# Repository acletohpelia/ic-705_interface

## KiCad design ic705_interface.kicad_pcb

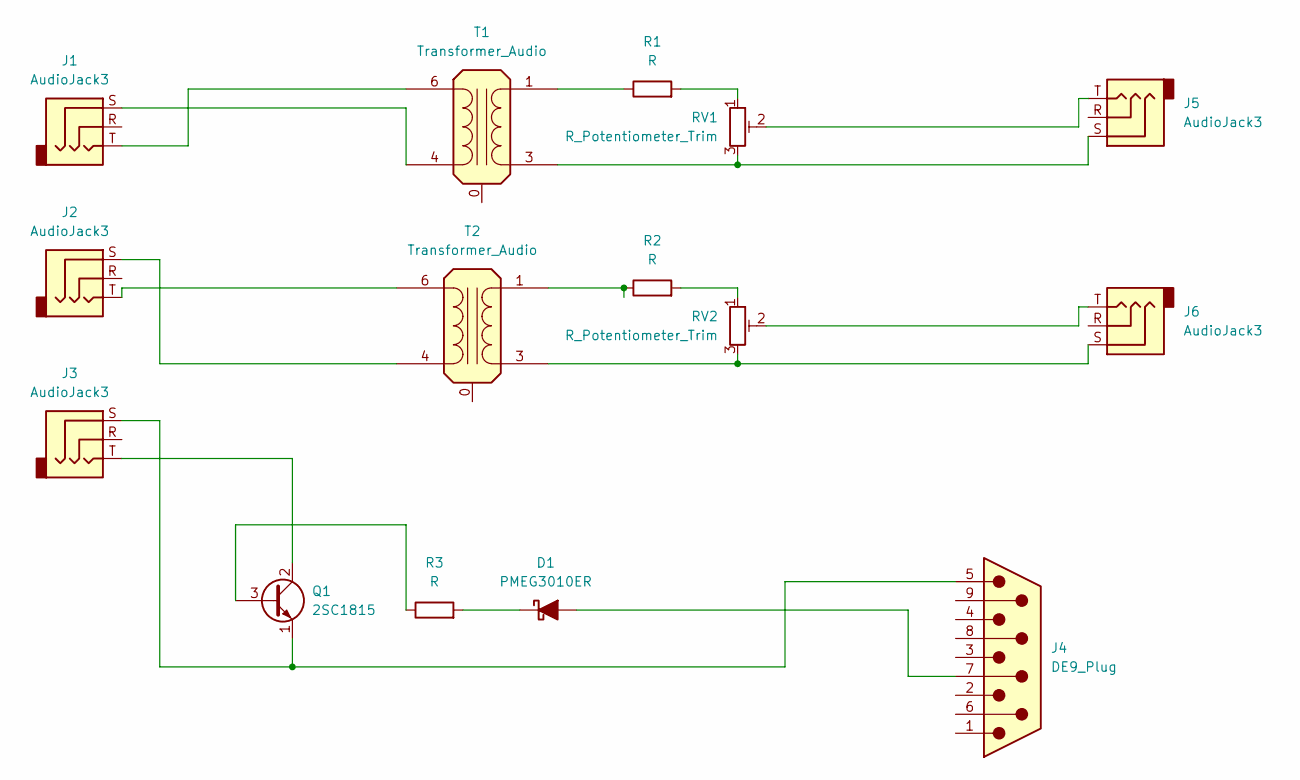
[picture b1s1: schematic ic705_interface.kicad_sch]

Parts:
D1: PMEG3010ER; D_DO-201AE_P15.24mm_Horizontal
J1, J2, J3, J5, J6: AudioJack3; Jack_3.5mm_CUI_SJ1-3533NG_Horizontal
J4: DE9_Plug; DSUB-9_Female_Vertical_P2.77x2.84mm_MountingHoles
Q1: 2SC1815; TO-92_Inline
R1, R2, R3: R; R_Axial_DIN0204_L3.6mm_D1.6mm_P1.90mm_Vertical
RV1, RV2: R_Potentiometer_Trim; Potentiometer_Piher_PT-10-V05_Vertical
T1, T2: Transformer_Audio; Transformer_NF_ETAL_1-1_P1200

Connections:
unnamed: D1.2 (A), J4.7
unnamed: D1.1 (K), R3.2
unnamed: J5.T, RV1.2
unnamed: J6.T, RV2.2
unnamed: Q1.3 (B), R3.1
unnamed: J3.T, Q1.2 (C)
unnamed: J3.S, J4.5, Q1.1 (E)
unnamed: R1.2, RV1.1
unnamed: R2.2, RV2.1
unnamed: J1.T, T1.6 (AA)
unnamed: J1.S, T1.4 (AB)
unnamed: J5.S, RV1.3, T1.3 (SA)
unnamed: R1.1, T1.1 (SB)
unnamed: J2.T, T2.6 (AA)
unnamed: J2.S, T2.4 (AB)
unnamed: J6.S, RV2.3, T2.3 (SA)
unnamed: R2.1, T2.1 (SB)

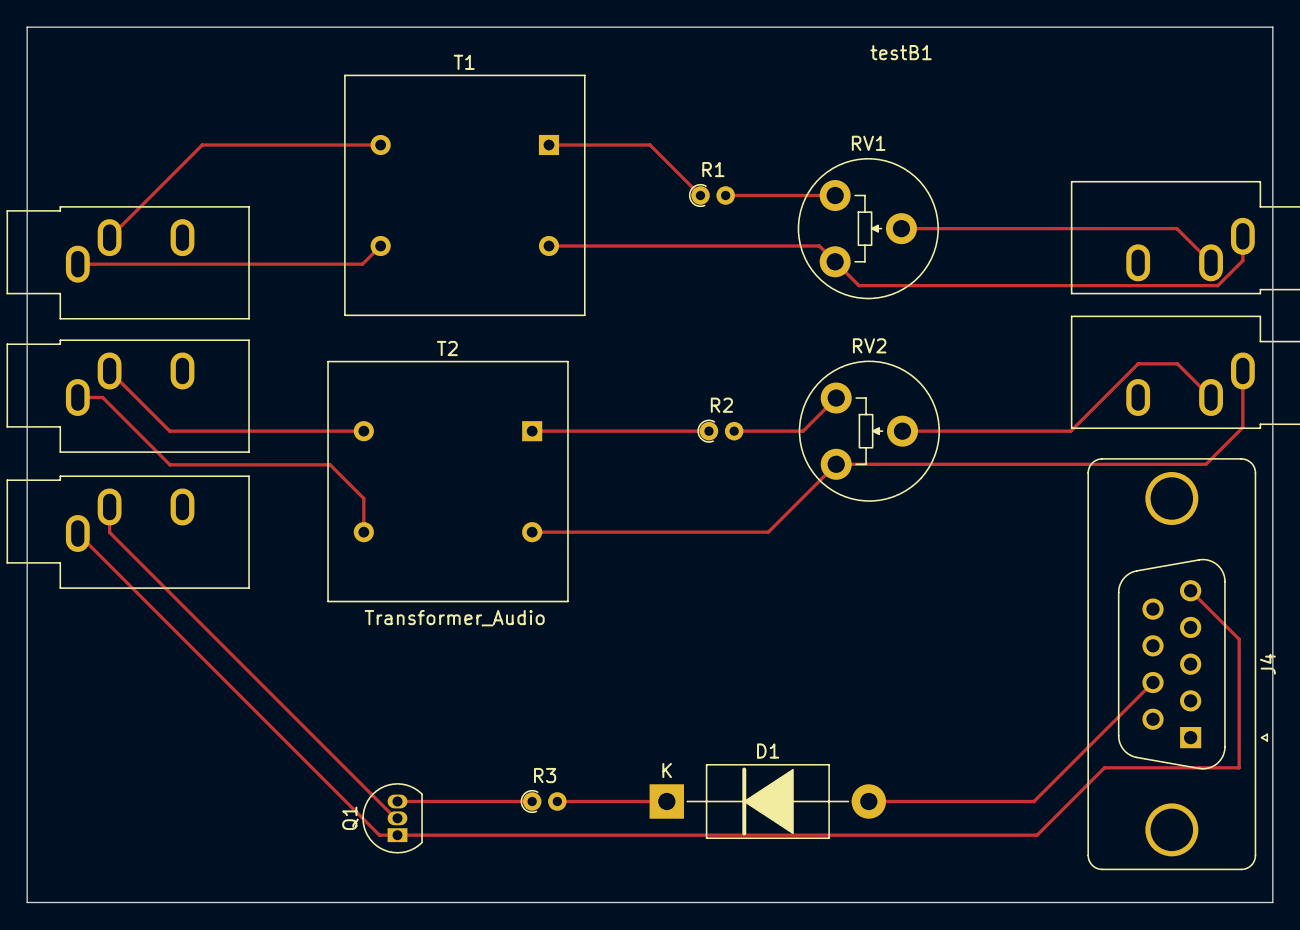
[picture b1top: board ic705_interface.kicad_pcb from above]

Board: 2 copper layers, 94.0 x 66.0 mm, 15 parts (0 on the bottom side), 17 nets.

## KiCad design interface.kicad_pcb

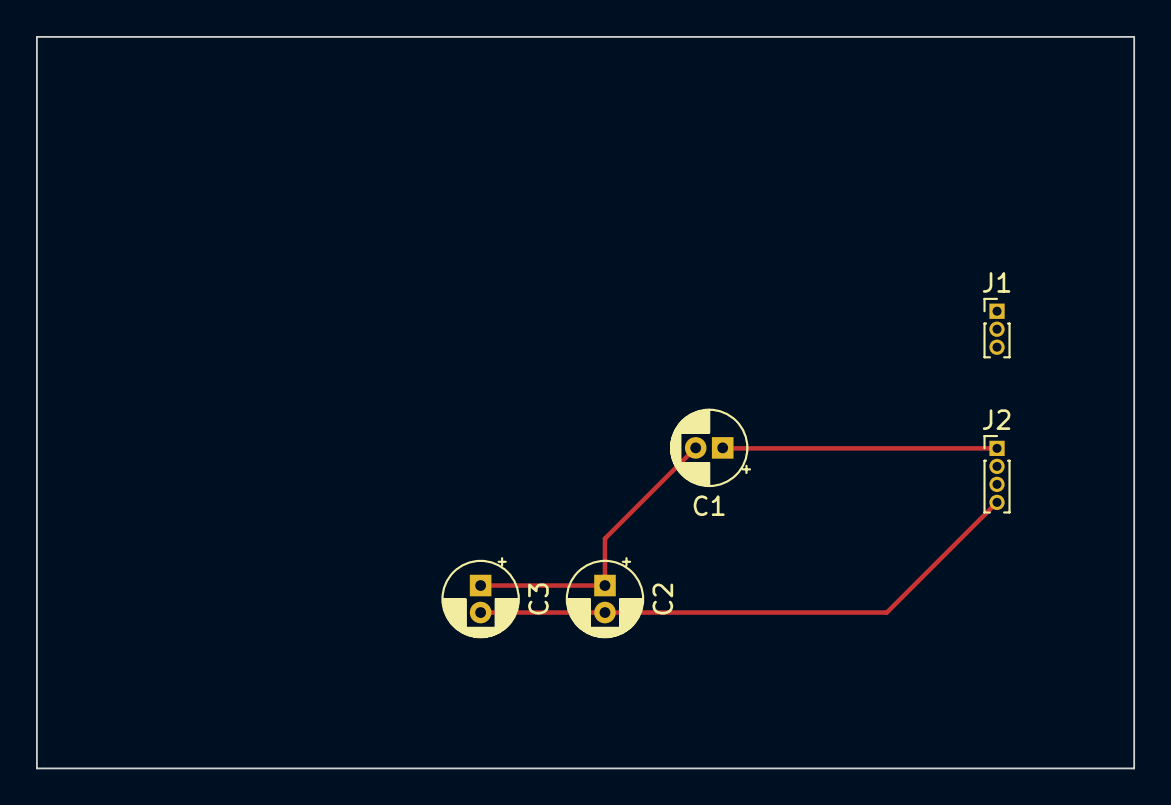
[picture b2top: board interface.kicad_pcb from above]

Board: 2 copper layers, 61.0 x 40.6 mm, 5 parts (0 on the bottom side), 3 nets.

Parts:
C1: 1uP; CP_Radial_D4.0mm_P1.50mm
C2: C; CP_Radial_D4.0mm_P1.50mm
C3: 0.001; CP_Radial_D4.0mm_P1.50mm
J1: audio; PinHeader_1x03_P1.00mm_Vertical
J2: mic&ptt; PinHeader_1x04_P1.00mm_Vertical

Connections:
unnamed: C1.1, J2.1
unnamed: C1.2, C2.1, C3.1
unnamed: C2.2, C3.2, J2.4
